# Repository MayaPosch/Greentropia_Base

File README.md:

# Greentropia Base Board #

The [Greentropia](http://www.nyantronics.com/greentropia.php "Greentropia") (formerly IoP) Base board is a fairly simple PCB aimed at monitoring and watering single plants or similar configurations. Its block diagram looks as follows:

This is the final board (without NodeMCU board installed):

This repository contains the full KiCad project for the board. More information about the Greentropia project can be found at [Nyantronics](http://nyantronics.com/ "Nyantronics.com").

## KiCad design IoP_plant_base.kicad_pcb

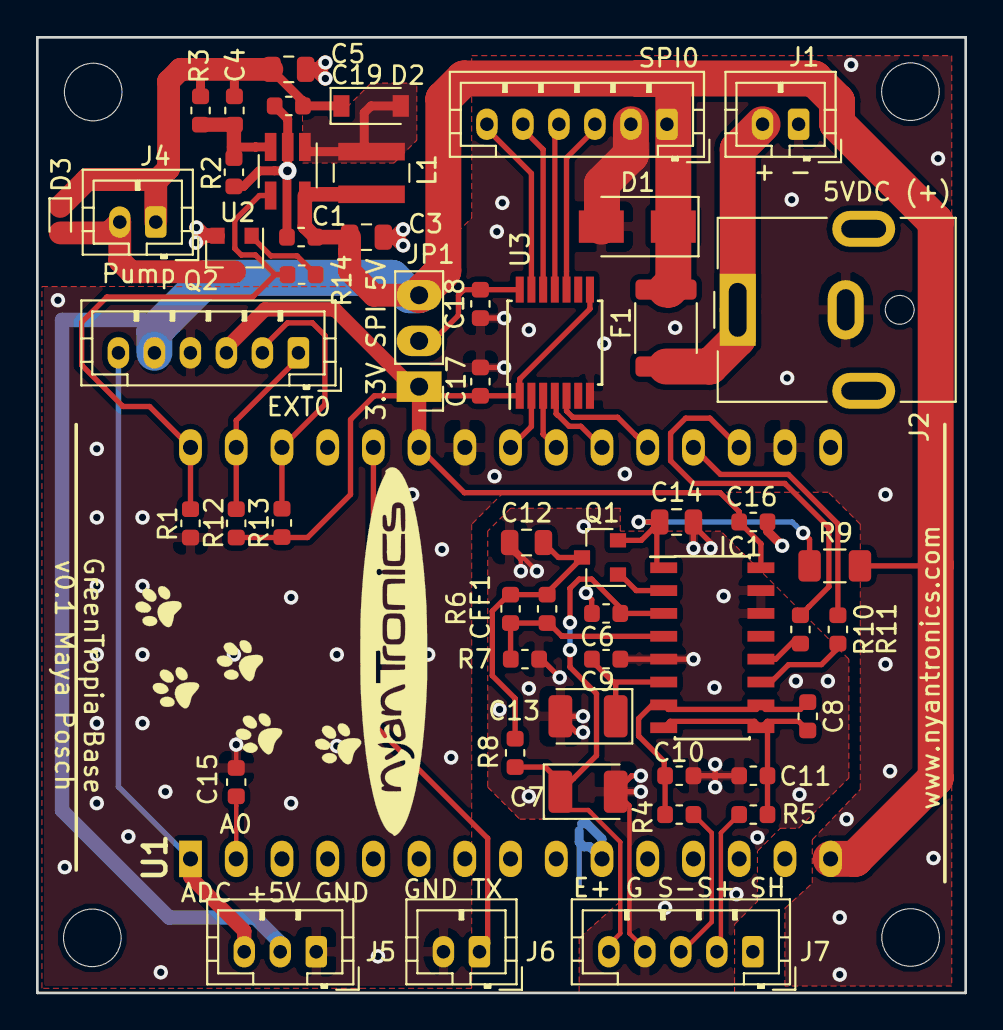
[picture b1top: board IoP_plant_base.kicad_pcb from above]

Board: 2 copper layers, 51.6 x 53.1 mm, 57 parts (0 on the bottom side), 38 nets.

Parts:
C1, C6, C9, C15, C16, C17, C18, C19: 100nF/50V; C_0603_1608Metric
C3, C12, C14: 10uF/16V; C_0805_2012Metric
C4: 220pF; C_0603_1608Metric
C5: 4.7uF/25V; C_0805_2012Metric
C7, C13: 100uF/6.3V; CP_EIA-3528-15_AVX-H
C8: 1uF/50V; C_0603_1608Metric
C10, C11: 10nF/50V; C_0603_1608Metric
CFF1: 1uF/50V; C_0603_1608Metric
D1: 1N4004; D_SMA
D2: MBR0520L; D_SOD-123
D3: ESD5Z12T1G; D_SOD-523
EXT0: Conn_01x06; JST_PH_B6B-PH-K_1x06_P2.00mm_Vertical
F1: Polyfuse; Fuse_1812_4532Metric
H1, H2, H3, H4: MountingHole; MountingHole_3.2mm_M3_DIN965
IC1: HX711; SOIC-16_3.9x9.9mm_Pitch1.27mm
J1, J4, J6: Conn_01x02; JST_PH_B2B-PH-K_1x02_P2.00mm_Vertical
J2: Jack-DC; BarrelJack_CUI_PJ-063AH_Horizontal
J5: Conn_01x03; JST_PH_B3B-PH-K_1x03_P2.00mm_Vertical
J7: Conn_01x05; JST_PH_B5B-PH-K_1x05_P2.00mm_Vertical
JP1: Jumper_3_Bridged12; PinHeader_1x03_P2.54mm_Vertical
L1: 10uH; L_Wuerth_MAPI-4020
Q1: BC857C; SOT-23
Q2: IRLML6244; SOT-23
R1, R12, R13: 4.7k; R_0603_1608Metric
R2: 13.3K; R_0603_1608Metric
R3: 117K; R_0603_1608Metric
R4, R5, R10, R11, R14: 100R; R_0603_1608Metric
R6: 2.0k; R_0603_1608Metric
R7: 1.0k; R_0603_1608Metric
R8: 10R; R_0603_1608Metric
R9: 100R; R_1206_3216Metric
SPI0: Conn_01x06; JST_PH_B6B-PH-K_1x06_P2.00mm_Vertical
U1: NodeMCUv2; DIP2286W64P254L4826H735Q30N
U2: LM27313XMF; SOT-23-5_HandSoldering
U3: TXB0104PWR; TSSOP-14_4.4x5mm_P0.65mm

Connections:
+3.3V: C16.2, C17.2, EXT0.3, IC1.16, JP1.1, R12.1, R13.1, U1.25, U3.1, U3.8
+5VDC: C1.1, C3.1, D1.1, EXT0.5, F1.1, J5.2, JP1.3, L1.1, R9.1, SPI0.1, U1.15, U2.5
+12VDC: C4.2, C5.1, C19.1, D2.1, D3.1, J4.1, R3.1
+12VRTN: D3.2, J4.2, Q2.3
/Dbg: J6.1, U1.26
/E+: C6.1, C7.1, IC1.3, J7.5, R8.2
/S+: J7.2, R5.1
/S-: J7.3, R4.2
ADC: EXT0.6, J5.3, U1.1
GND: C1.2, C3.2, C5.2, C6.2, C7.2, C9.1, C10.1, C11.1, C12.2, C13.2, C14.2, C15.2, C16.1, C17.1, C18.1, C19.2, D1.2, EXT0.4, IC1.5, IC1.14, IC1.15, J1.1, J2.2, J5.1, J6.2, J7.1, J7.4, Q2.2, R1.2, R2.2, R7.2, SPI0.2, U1.10, U1.14, U1.17, U1.24, U2.2, U3.7
HX711_DOUT: R10.1, U1.18
HX711_SCK: R11.1, U1.19
unnamed: C4.1, R2.1, R3.2, U2.3
unnamed: C8.1, C10.2, IC1.7, IC1.10, R4.1
unnamed: C8.2, C11.2, IC1.8, IC1.9, R5.2
unnamed: C12.1, CFF1.1, Q1.3, R6.1, R8.1
unnamed: C9.2, C13.1, IC1.6
unnamed: C14.1, IC1.1, Q1.2, R9.2
unnamed: C15.1, U1.2
unnamed: C18.2, JP1.2, U3.14
unnamed: CFF1.2, IC1.4, R6.2, R7.1
unnamed: D2.2, L1.2, U2.1
unnamed: F1.2, J1.2, J2.1
unnamed: IC1.2, Q1.1
unnamed: IC1.11, R11.2
unnamed: IC1.12, R10.2
unnamed: Q2.1, R14.2
PUMP_EN: R1.1, R14.1, U1.30, U2.4
SCL: EXT0.1, R12.2, U1.29
SDA: EXT0.2, R13.2, U1.28
SPI_CLK: U1.23, U3.2
SPI_CLK_5V: SPI0.6, U3.13
SPI_CSN: U1.20, U3.5
SPI_CSN_5V: SPI0.3, U3.10
SPI_MISO: U1.22, U3.3
SPI_MISO_5V: SPI0.5, U3.12
SPI_MOSI: U1.21, U3.4
SPI_MOSI_5V: SPI0.4, U3.11

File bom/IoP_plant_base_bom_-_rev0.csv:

"Id";"Designator";"Package";"Quantity";"Designation";"Supplier and ref";
1;"U1";"DIP2286W64P254L4826H735Q30N";1;"NodeMCUv2";;;
2;"SPI0,EXT0";"JST_PH_B6B-PH-K_1x06_P2.00mm_Vertical";2;"Conn_01x06";;;
3;"J4,J1,J6";"JST_PH_B2B-PH-K_1x02_P2.00mm_Vertical";3;"Conn_01x02";;;
4;"U2";"SOT-23-5_HandSoldering";1;"LM27313XMF";;;
5;"U3";"TSSOP-14_4.4x5mm_P0.65mm";1;"TXB0104PWR";;;
6;"R14,R5,R4,R10,R11";"R_0603_1608Metric";5;"100";;;
7;"R13,R12,R1";"R_0603_1608Metric";3;"4.7k";;;
8;"Q2";"SOT-23";1;"IRLML6244";;;
9;"JP1";"PinHeader_1x03_P2.54mm_Vertical";1;"Jumper_3_Bridged12";;;
10;"D3";"D_SOD-523";1;"ESD5Z12T1G";;;
11;"C19,C18,C17,C1,C16,C6";"C_0603_1608Metric";6;"100nF";;;
12;"C5";"C_0805_2012Metric";1;"4.7uF";;;
14;"J2";"BarrelJack_CUI_PJ-063AH_Horizontal";1;"Jack-DC";;;
15;"J5";"JST_PH_B3B-PH-K_1x03_P2.00mm_Vertical";1;"Conn_01x03";;;
16;"J7";"JST_PH_B5B-PH-K_1x05_P2.00mm_Vertical";1;"Conn_01x05";;;
17;"D1";"D_SMA";1;"1N4004";;;
18;"F1";"Fuse_1812_4532Metric";1;"Polyfuse";;;
19;"R9";"R_1206_3216Metric";1;"100R";;;
20;"C3,C12,C14";"C_0805_2012Metric";3;"10uF";;;
21;"C15,C9";"C_0603_1608Metric";2;"0.1uF";;;
22;"C4";"C_0603_1608Metric";1;"220pF";;;
23;"C8,CFF1";"C_0603_1608Metric";2;"1uF";;;
24;"D2";"D_SOD-123";1;"MBR0520L";;;
25;"R7";"R_0603_1608Metric";1;"1.0k";;;
26;"R6";"R_0603_1608Metric";1;"2.0k";;;
27;"R3";"R_0603_1608Metric";1;"117K";;;
28;"R2";"R_0603_1608Metric";1;"13.3K";;;
29;"L1";"L_Wuerth_MAPI-4020";1;"10uH";;;
30;"IC1";"SOIC-16_3.9x9.9mm_Pitch1.27mm";1;"HX711";;;
31;"R8";"R_0603_1608Metric";1;"10R";;;
32;"Q1";"SOT-23";1;"BC857C";;;
33;"C13,C7";"CP_EIA-3528-15_AVX-H";2;"100uF/6.3V";;;
34;"C11,C10";"C_0603_1608Metric";2;"10nF";;;

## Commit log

2018-09-07 Initial commit. Added SPI breakout with level converter.
2018-09-12 Started routing boost converter. TODO: footprint name fixing.
2018-12-22 Finish initial PCB routing.
2018-12-26 * renamed SPI_INT to SPI_CSN * remapped SPI pins to HSPI (no overlap with internal flash) * renamed time critical / permanently driven HX711 pseudo-SPI pins to GPIO1 / GPIO3 such that RXD0 can overri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
2018-12-26 PCB schematic and layout updated. More changes to actual footprints (all headers are now vertical), some BOM info added. Re-routed DCDC section. *** TODO *** rules-check everything including pinouts.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
2018-12-27 Generate Gerber files. Small silkscreen tweaks & clean-up.
2018-12-27 Add ZIP file with Gerbers.
2019-01-03 fixed inconsistent parts values, preliminary BOM created (missing Mouser part numbers)
2019-01-20 updated BOM info according to Mouser order. Note: consider migrating to ME2149F SO8 for next rev. (higher current, ~30ct vs. 1.15€)
2019-03-04 adds GreenTropia Base functional block diagram (draw.io format)
2019-03-12 Add README.
